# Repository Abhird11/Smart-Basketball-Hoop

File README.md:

This is our senior design project

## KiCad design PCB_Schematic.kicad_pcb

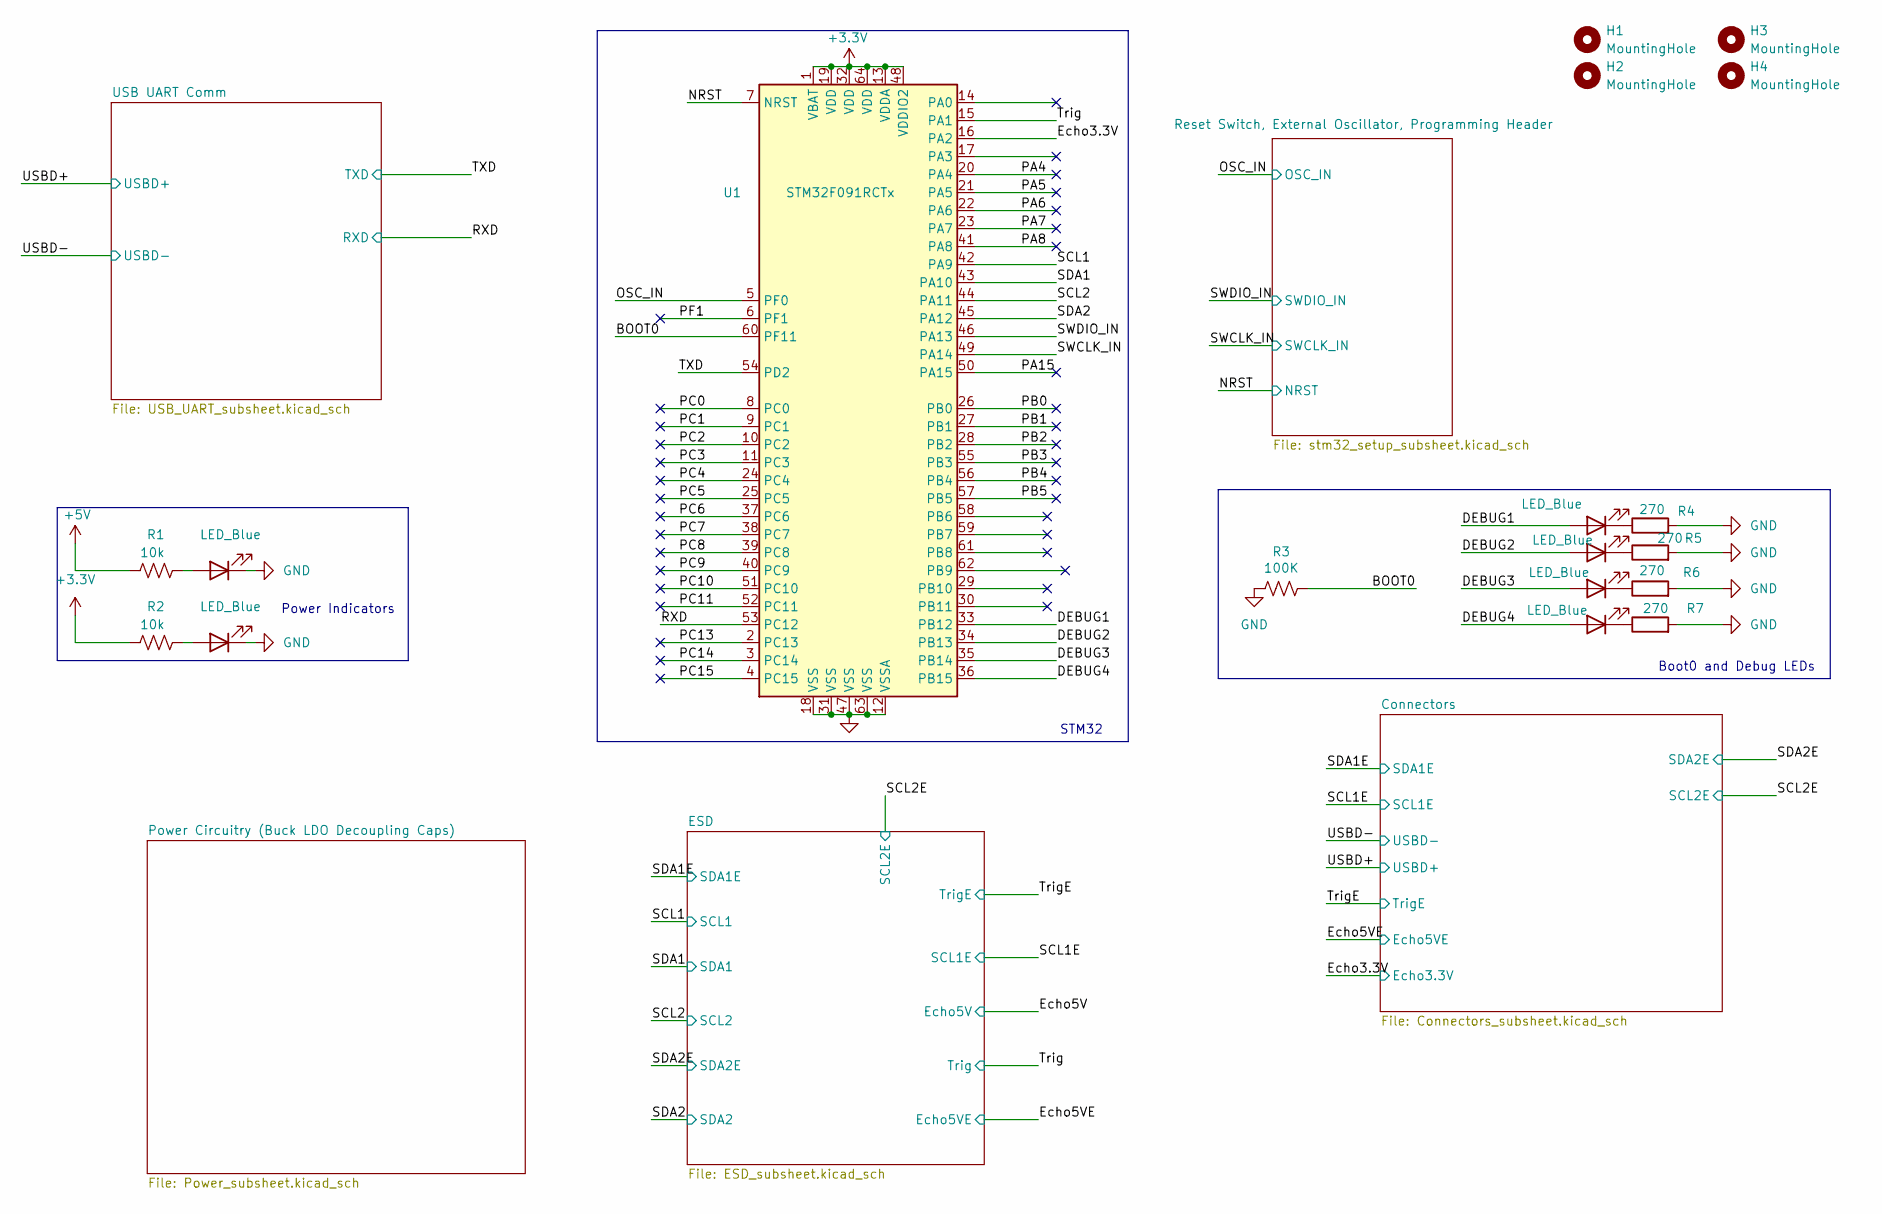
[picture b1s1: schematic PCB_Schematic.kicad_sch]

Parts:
D1, D2, D3, D4, D5, D6: LED_Blue; LED_0805_2012Metric_Pad1.15x1.40mm_HandSolder
H1, H2, H3, H4: MountingHole; MountingHole_2.2mm_M2
R1, R2: 10k; R_0805_2012Metric_Pad1.20x1.40mm_HandSolder
R3: 100K; R_0805_2012Metric_Pad1.20x1.40mm_HandSolder
R4, R5, R6, R7: 270; C_0805_2012Metric_Pad1.18x1.45mm_HandSolder
U1: STM32F091RCTx; LQFP-64_10x10mm_P0.5mm

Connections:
+3.3V: R2.2, U1.1 (VBAT), U1.13 (VDDA), U1.19 (VDD), U1.32 (VDD), U1.48 (VDDIO2), U1.64 (VDD); also elsewhere on the board
+5V: R1.2; also elsewhere on the board
/BOOT0: R3.1, U1.60 (PF11)
/DEBUG1: D3.2 (A), U1.33 (PB12)
/DEBUG2: D4.2 (A), U1.34 (PB13)
/DEBUG3: D5.2 (A), U1.35 (PB14)
/DEBUG4: D6.2 (A), U1.36 (PB15)
/Echo3.3V: U1.16 (PA2); also elsewhere on the board
/NRST: U1.7 (NRST); also elsewhere on the board
/OSC_IN: U1.5 (PF0); also elsewhere on the board
/PA4: U1.20 (PA4)
/PA5: U1.21 (PA5)
/PA6: U1.22 (PA6)
/PA7: U1.23 (PA7)
/PA8: U1.41 (PA8)
/PA15: U1.50 (PA15)
/PB0: U1.26 (PB0)
/PB1: U1.27 (PB1)
/PB2: U1.28 (PB2)
/PB3: U1.55 (PB3)
/PB4: U1.56 (PB4)
/PB5: U1.57 (PB5)
/PC0: U1.8 (PC0)
/PC1: U1.9 (PC1)
/PC2: U1.10 (PC2)
/PC3: U1.11 (PC3)
/PC4: U1.24 (PC4)
/PC5: U1.25 (PC5)
/PC6: U1.37 (PC6)
/PC7: U1.38 (PC7)
/PC8: U1.39 (PC8)
/PC9: U1.40 (PC9)
/PC10: U1.51 (PC10)
/PC11: U1.52 (PC11)
/PC13: U1.2 (PC13)
/PC14: U1.3 (PC14)
/PC15: U1.4 (PC15)
/PF1: U1.6 (PF1)
/RXD: U1.53 (PC12); also elsewhere on the board
/SCL1: U1.42 (PA9); also elsewhere on the board
/SCL2: U1.44 (PA11); also elsewhere on the board
/SDA1: U1.43 (PA10); also elsewhere on the board
/SDA2: U1.45 (PA12); also elsewhere on the board
/SWCLK_IN: U1.49 (PA14); also elsewhere on the board
/SWDIO_IN: U1.46 (PA13); also elsewhere on the board
/TXD: U1.54 (PD2); also elsewhere on the board
/Trig: U1.15 (PA1); also elsewhere on the board
GND: D1.1 (K), D2.1 (K), R3.2, R4.2, R5.2, R6.2, R7.2, U1.12 (VSSA), U1.18 (VSS), U1.31 (VSS), U1.47 (VSS), U1.63 (VSS); also elsewhere on the board
unnamed: D1.2 (A), R1.1
unnamed: D2.2 (A), R2.1
unnamed: D3.1 (K), R4.1
unnamed: D4.1 (K), R5.1
unnamed: D5.1 (K), R6.1
unnamed: D6.1 (K), R7.1

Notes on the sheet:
STM32
Boot0 and Debug LEDs
Power Indicators

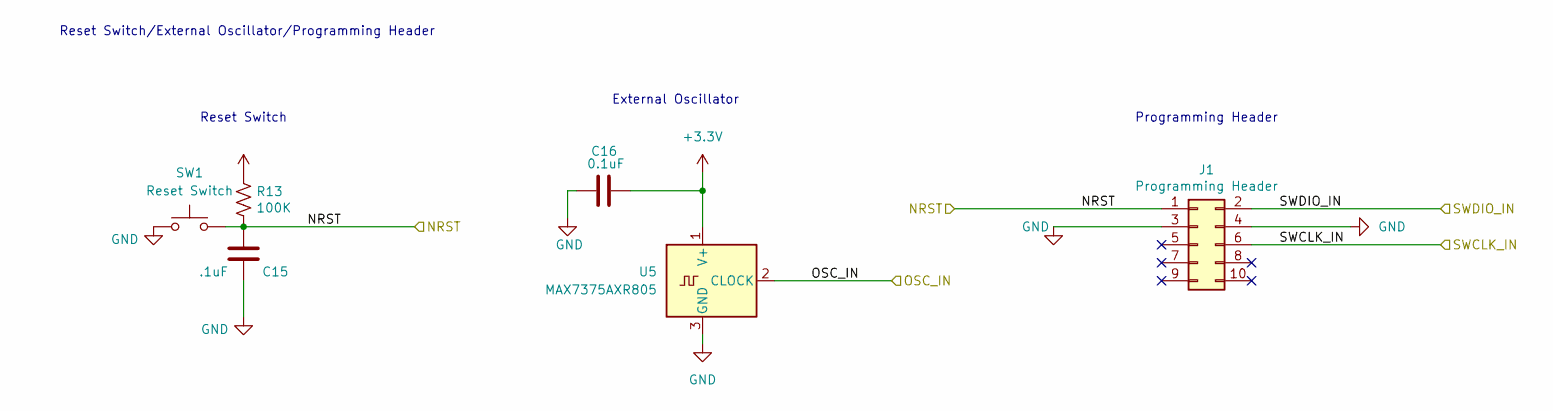
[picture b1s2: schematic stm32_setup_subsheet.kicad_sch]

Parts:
C15: .1uF; C_0805_2012Metric_Pad1.18x1.45mm_HandSolder
C16: 0.1uF; C_0805_2012Metric_Pad1.18x1.45mm_HandSolder
J1: Programming Header; IDC-Header_2x05_P2.54mm_Vertical
R13: 100K; R_0805_2012Metric_Pad1.20x1.40mm_HandSolder
SW1: Reset Switch; SW_TS04-66-55-BK-160-SMT
U5: MAX7375AXR805; SOT-323_SC-70_Handsoldering

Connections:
+3.3V: C16.2, R13.1, U5.1 (V+); also elsewhere on the board
/NRST: C15.1, J1.1, R13.2, SW1.2; also elsewhere on the board
/OSC_IN: U5.2 (CLOCK); also elsewhere on the board
/SWCLK_IN: J1.6; also elsewhere on the board
/SWDIO_IN: J1.2; also elsewhere on the board
GND: C15.2, C16.1, J1.3, J1.4, SW1.1, U5.3 (GND); also elsewhere on the board

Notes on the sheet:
Programming Header
Reset Switch/External Oscillator/Programming Header
Reset Switch
External Oscillator

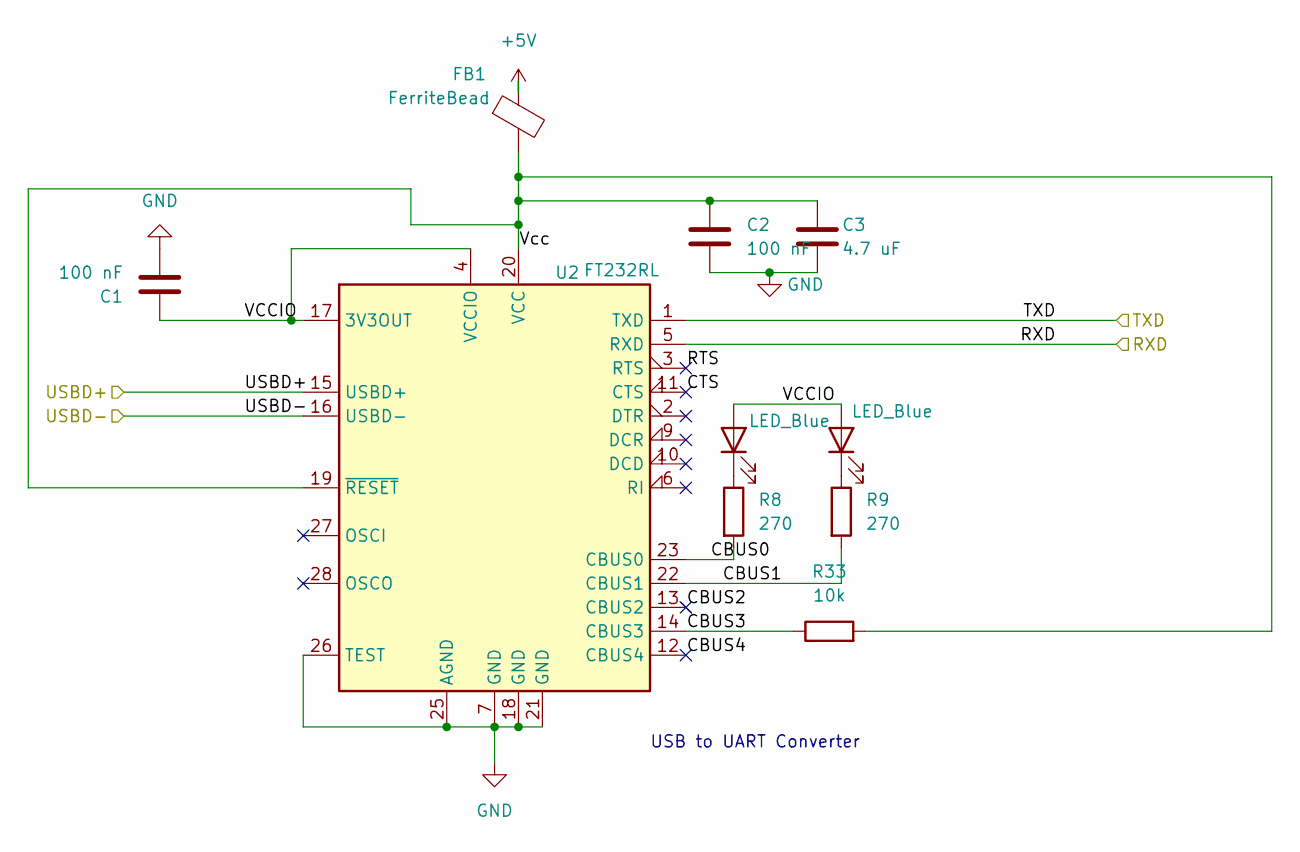
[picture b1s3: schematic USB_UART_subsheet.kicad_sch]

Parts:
C1, C2: 100 nF; C_0805_2012Metric_Pad1.18x1.45mm_HandSolder
C3: 4.7 uF; C_0805_2012Metric_Pad1.18x1.45mm_HandSolder
D7, D8: LED_Blue; LED_0805_2012Metric_Pad1.15x1.40mm_HandSolder
FB1: FerriteBead; FB
R8: 270; R_0805_2012Metric_Pad1.20x1.40mm_HandSolder
R9: 270; C_0805_2012Metric_Pad1.18x1.45mm_HandSolder
R33: 10k; R_0805_2012Metric_Pad1.20x1.40mm_HandSolder
U2: FT232RL; Project_FT232

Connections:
+5V: FB1.1; also elsewhere on the board
/RXD: U2.5 (RXD); also elsewhere on the board
/TXD: U2.1 (TXD); also elsewhere on the board
/USB UART Comm/CBUS0: R8.2, U2.23 (CBUS0)
/USB UART Comm/CBUS1: R9.2, U2.22 (CBUS1)
/USB UART Comm/CBUS2: U2.13 (CBUS2)
/USB UART Comm/CBUS3: R33.1, U2.14 (CBUS3)
/USB UART Comm/CBUS4: U2.12 (CBUS4)
/USB UART Comm/CTS: U2.11 (CTS)
/USB UART Comm/RTS: U2.3 (RTS)
/USB UART Comm/VCCIO: C1.1, D7.2 (A), D8.2 (A), U2.4 (VCCIO), U2.17 (3V3OUT)
/USB UART Comm/Vcc: C2.1, C3.1, FB1.2, R33.2, U2.19 (~RESET), U2.20 (VCC)
/USBD+: U2.15 (USBD+); also elsewhere on the board
/USBD-: U2.16 (USBD-); also elsewhere on the board
GND: C1.2, C2.2, C3.2, U2.7 (GND), U2.18 (GND), U2.21 (GND), U2.25 (AGND), U2.26 (TEST); also elsewhere on the board
unnamed: D7.1 (K), R8.1
unnamed: D8.1 (K), R9.1

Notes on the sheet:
USB to UART Converter

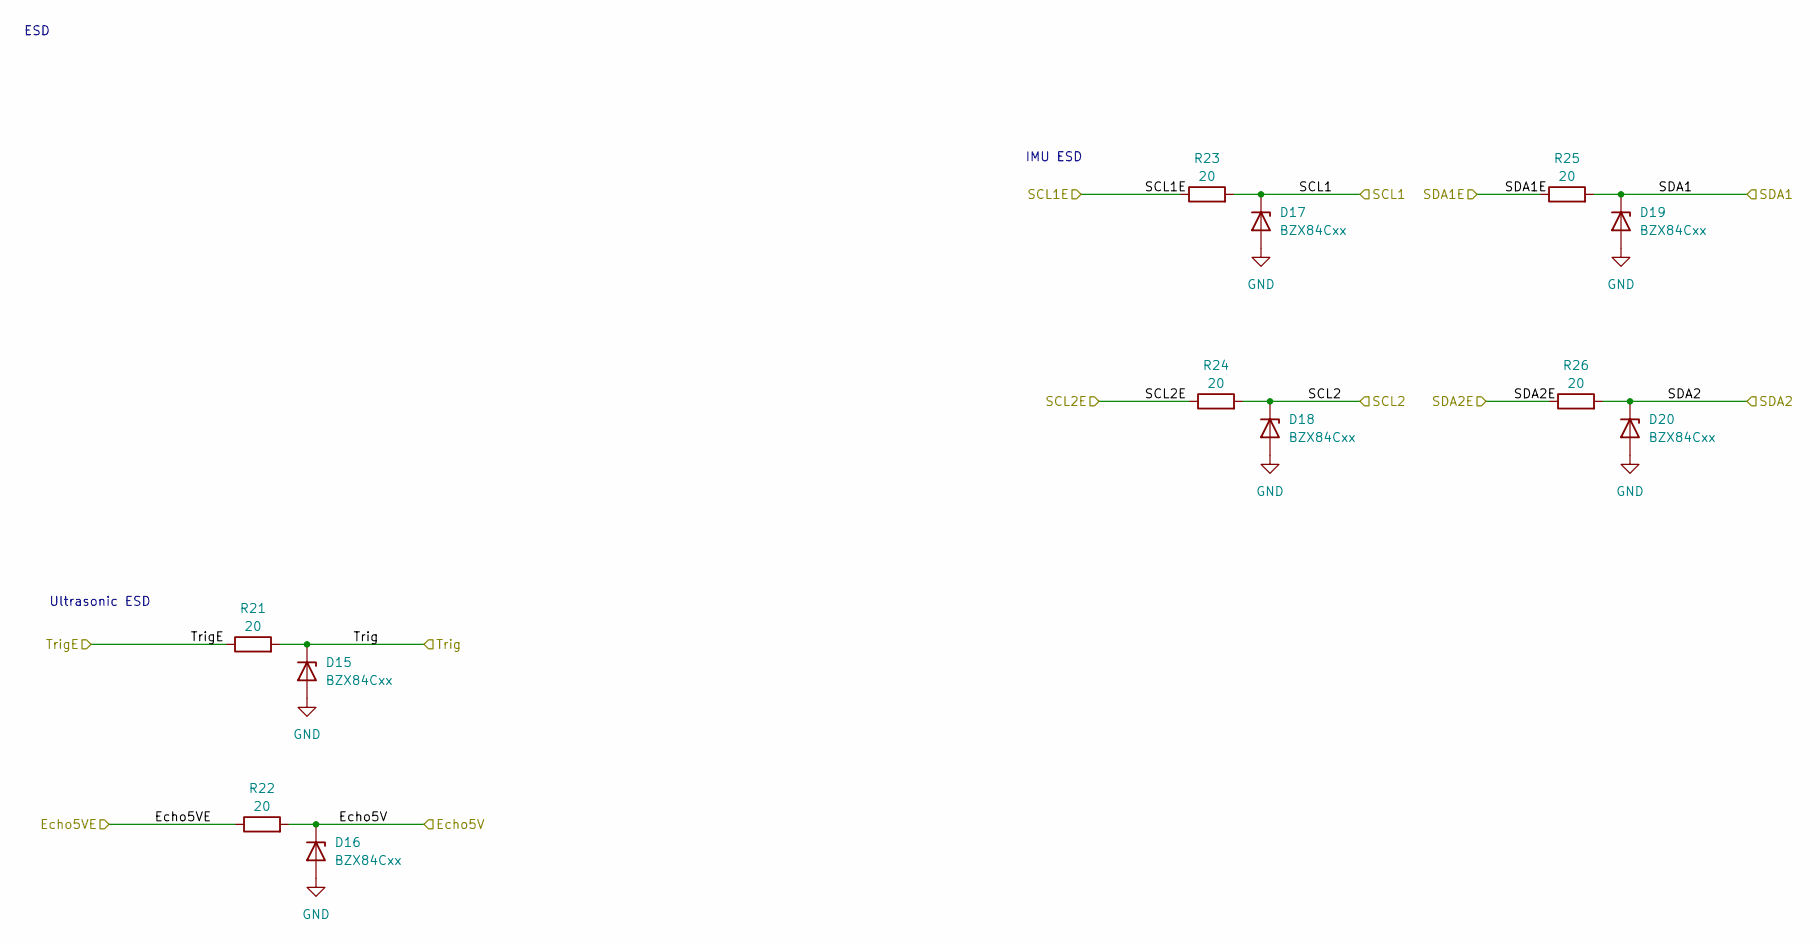
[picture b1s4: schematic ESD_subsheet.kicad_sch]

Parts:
D15, D16, D17, D18, D19, D20: BZX84Cxx; SOT-23
R21, R22, R23, R24, R25, R26: 20; R_0805_2012Metric_Pad1.20x1.40mm_HandSolder

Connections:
/Echo5V: D16.3 (K), R22.2
/Echo5VE: R22.1; also elsewhere on the board
/SCL1: D17.3 (K), R23.2; also elsewhere on the board
/SCL1E: R23.1; also elsewhere on the board
/SCL2: D18.3 (K), R24.2; also elsewhere on the board
/SCL2E: R24.1; also elsewhere on the board
/SDA1: D19.3 (K), R25.2; also elsewhere on the board
/SDA1E: R25.1; also elsewhere on the board
/SDA2: D20.3 (K), R26.2; also elsewhere on the board
/SDA2E: R26.1; also elsewhere on the board
/Trig: D15.3 (K), R21.2; also elsewhere on the board
/TrigE: R21.1; also elsewhere on the board
GND: D15.1 (A), D16.1 (A), D17.1 (A), D18.1 (A), D19.1 (A), D20.1 (A); also elsewhere on the board

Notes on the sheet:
IMU ESD
ESD
Ultrasonic ESD

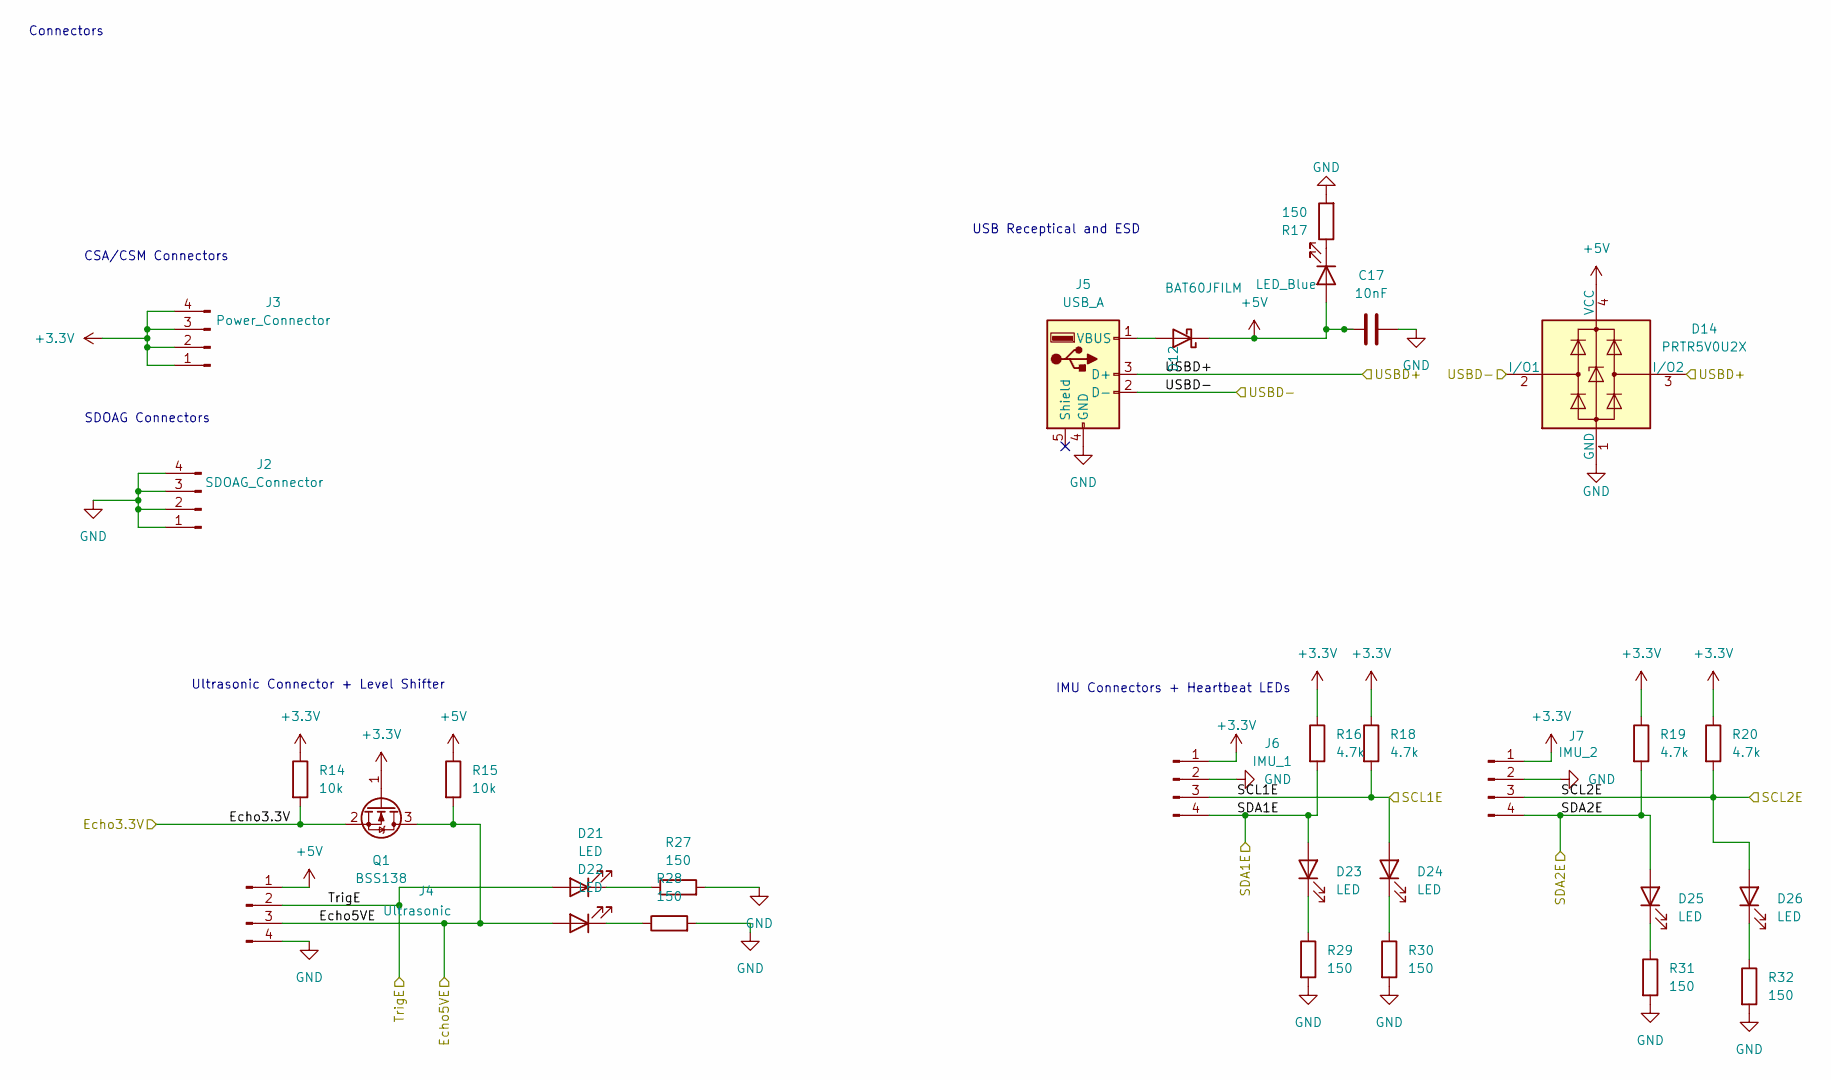
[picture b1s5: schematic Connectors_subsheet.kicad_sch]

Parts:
C17: 10nF; C_0805_2012Metric_Pad1.18x1.45mm_HandSolder
D12: BAT60JFILM; D_SOD-323_HandSoldering
D13: LED_Blue; LED_0805_2012Metric_Pad1.15x1.40mm_HandSolder
D14: PRTR5V0U2X; PRT
D21, D22, D23, D24, D25, D26: LED; LED_0805_2012Metric_Pad1.15x1.40mm_HandSolder
J2: SDOAG_Connector; CONN_B4B-XH-A_JSTProject
J3: Power_Connector; CONN_B4B-XH-A_JSTProject
J4: Ultrasonic; CONN_B4B-XH-A_JSTProject
J5: USB_A; USB_A_Receptacle_GCT_USB1046
J6: IMU_1; CONN_B4B-XH-A_JSTProject
J7: IMU_2; CONN_B4B-XH-A_JSTProject
Q1: BSS138; SOT-23-3
R14, R15: 10k; R_0805_2012Metric_Pad1.20x1.40mm_HandSolder
R16, R18, R19, R20: 4.7k; R_0805_2012Metric_Pad1.20x1.40mm_HandSolder
R17, R27, R28, R29, R30, R31, R32: 150; R_0805_2012Metric_Pad1.20x1.40mm_HandSolder

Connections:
+3.3V: J3.1, J3.2, J3.3, J3.4, J6.1, J7.1, Q1.1 (G), R14.1, R16.1, R18.1, R19.1, R20.1; also elsewhere on the board
+5V: C17.1, D12.1 (K), D13.2 (A), D14.4 (VCC), J4.1, R15.1; also elsewhere on the board
/Echo3.3V: Q1.2 (S), R14.2; also elsewhere on the board
/Echo5VE: D22.2 (A), J4.3, Q1.3 (D), R15.2; also elsewhere on the board
/SCL1E: D24.2 (A), J6.3, R18.2; also elsewhere on the board
/SCL2E: D26.2 (A), J7.3, R20.2; also elsewhere on the board
/SDA1E: D23.2 (A), J6.4, R16.2; also elsewhere on the board
/SDA2E: D25.2 (A), J7.4, R19.2; also elsewhere on the board
/TrigE: D21.2 (A), J4.2; also elsewhere on the board
/USBD+: D14.3 (I/O2), J5.3 (D+); also elsewhere on the board
/USBD-: D14.2 (I/O1), J5.2 (D-); also elsewhere on the board
GND: C17.2, D14.1 (GND), J2.1, J2.2, J2.3, J2.4, J4.4, J5.4 (GND), J6.2, J7.2, R17.2, R27.2, R28.2, R29.2, R30.2, R31.2, R32.2; also elsewhere on the board
unnamed: D12.2 (A), J5.1 (VBUS)
unnamed: D13.1 (K), R17.1
unnamed: D21.1 (K), R27.1
unnamed: D22.1 (K), R28.1
unnamed: D23.1 (K), R29.1
unnamed: D24.1 (K), R30.1
unnamed: D25.1 (K), R31.1
unnamed: D26.1 (K), R32.1

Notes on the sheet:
Ultrasonic Connector + Level Shifter
Connectors
SDOAG Connectors
USB Receptical and ESD
IMU Connectors + Heartbeat LEDs
CSA/CSM Connectors

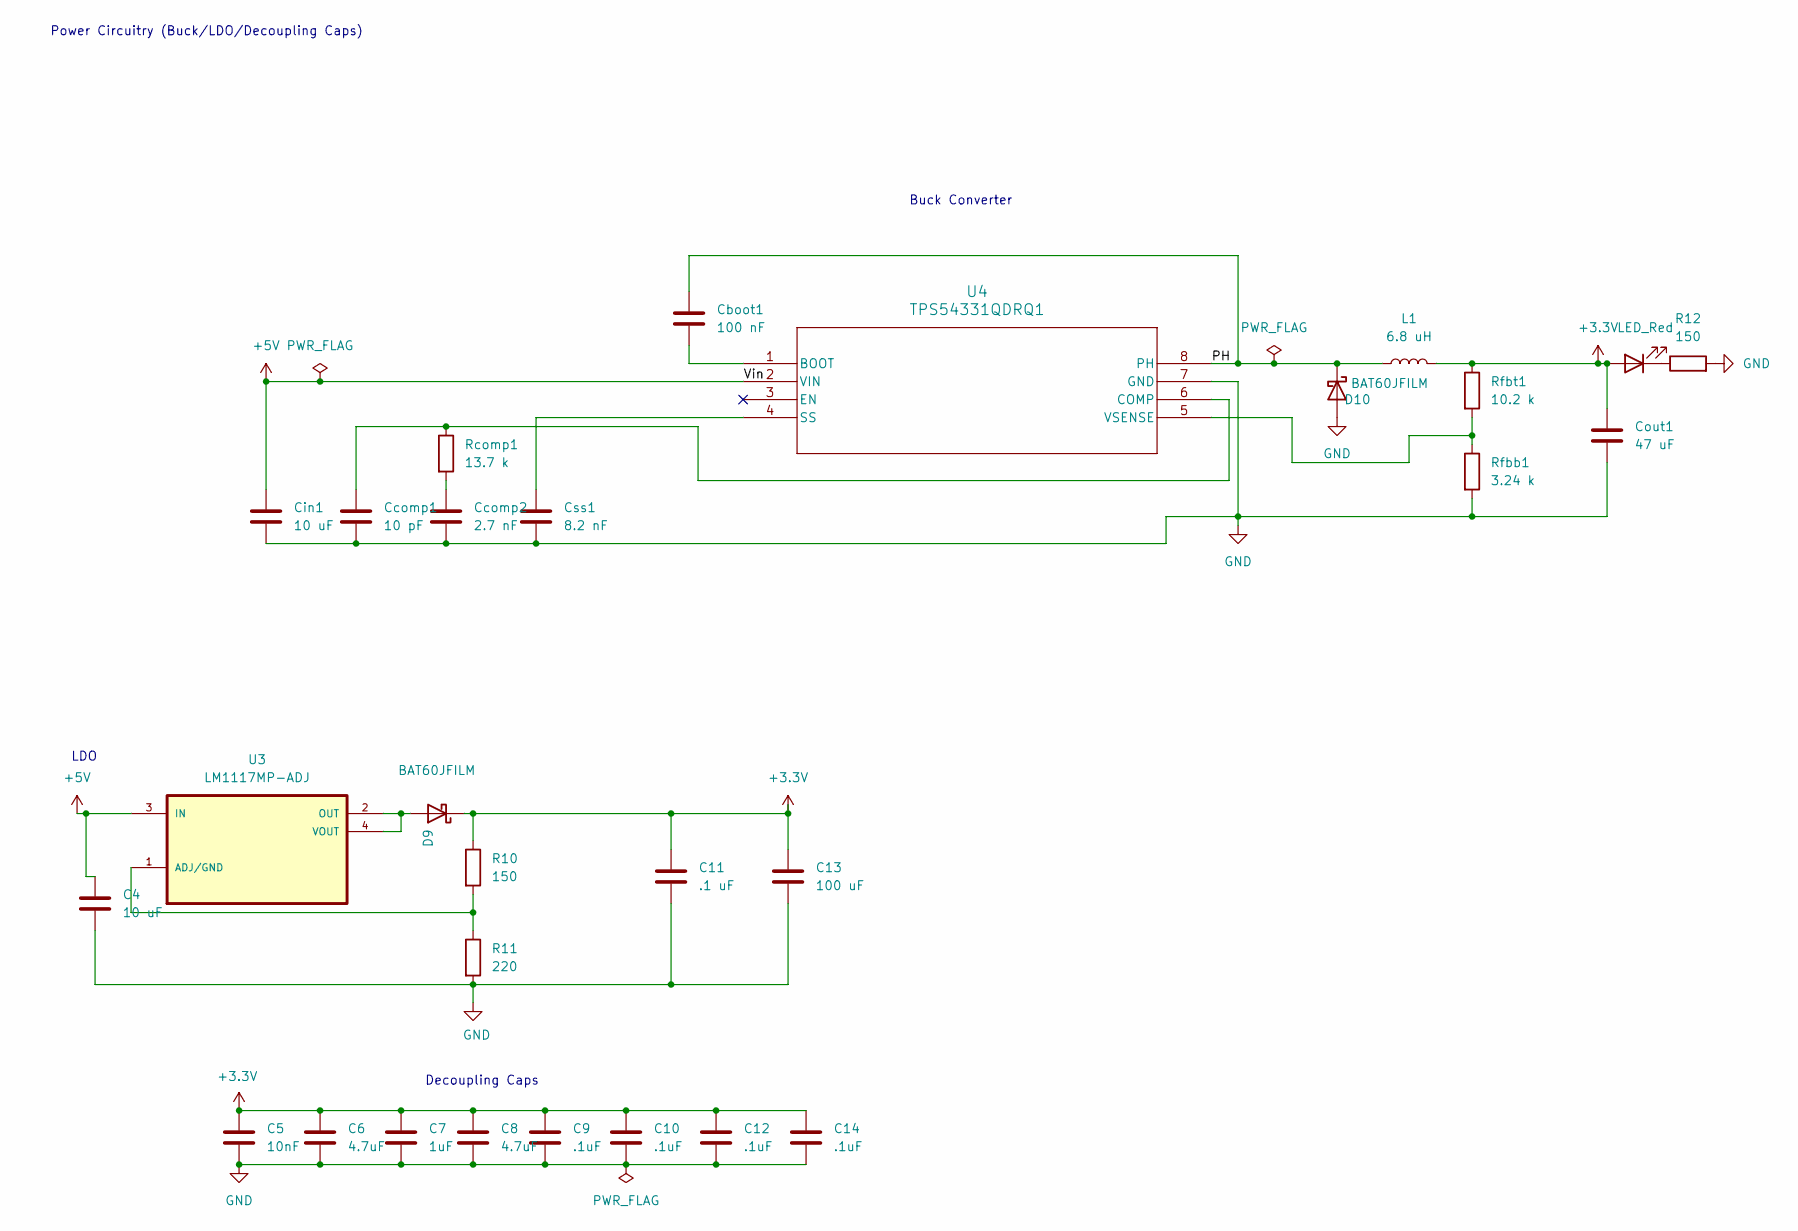
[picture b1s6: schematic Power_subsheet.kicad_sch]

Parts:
C4: 10 uF; C_0805_2012Metric_Pad1.18x1.45mm_HandSolder
C5: 10nF; C_0805_2012Metric_Pad1.18x1.45mm_HandSolder
C6, C8: 4.7uF; C_0805_2012Metric_Pad1.18x1.45mm_HandSolder
C7: 1uF; C_0805_2012Metric_Pad1.18x1.45mm_HandSolder
C9, C10, C12, C14: .1uF; C_0805_2012Metric_Pad1.18x1.45mm_HandSolder
C11: .1 uF; C_0805_2012Metric_Pad1.18x1.45mm_HandSolder
C13: 100 uF; C_0805_2012Metric_Pad1.18x1.45mm_HandSolder
Cboot1: 100 nF; R_0805_2012Metric_Pad1.20x1.40mm_HandSolder
Ccomp1: 10 pF; C_0805_2012Metric_Pad1.18x1.45mm_HandSolder
Ccomp2: 2.7 nF; C_0805_2012Metric_Pad1.18x1.45mm_HandSolder
Cin1: 10 uF; C_0805_2012Metric_Pad1.18x1.45mm_HandSolder
Cout1: 47 uF; C_0805_2012Metric_Pad1.18x1.45mm_HandSolder
Css1: 8.2 nF; C_0805_2012Metric_Pad1.18x1.45mm_HandSolder
D9: BAT60JFILM; D_SOD-323_HandSoldering
D10: BAT60JFILM; D_SOD-123
D11: LED_Red; LED_0805_2012Metric_Pad1.15x1.40mm_HandSolder
L1: 6.8 uH; inductor
R10, R12: 150; R_0805_2012Metric_Pad1.20x1.40mm_HandSolder
R11: 220; R_0805_2012Metric_Pad1.20x1.40mm_HandSolder
Rcomp1: 13.7 k; R_0805_2012Metric_Pad1.20x1.40mm_HandSolder
Rfbb1: 3.24 k; R_0805_2012Metric_Pad1.20x1.40mm_HandSolder
Rfbt1: 10.2 k; R_0805_2012Metric_Pad1.20x1.40mm_HandSolder
U3: LM1117MP-ADJ; REALWORKLDOFT
U4: TPS54331QDRQ1; Project_TPS

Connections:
+3.3V: C5.1, C6.1, C7.1, C8.1, C9.1, C10.1, C11.1, C12.1, C13.1, C14.1, Cout1.1, D9.1 (K), D11.2 (A), L1.2, R10.1, Rfbt1.1; also elsewhere on the board
+5V: C4.1, Cin1.1, U3.3 (IN), U4.2 (VIN); also elsewhere on the board
/Power Circuitry (Buck LDO Decoupling Caps)/PH: Cboot1.1, D10.1 (K), L1.1, U4.8 (PH)
GND: C4.2, C5.2, C6.2, C7.2, C8.2, C9.2, C10.2, C11.2, C12.2, C13.2, C14.2, Ccomp1.2, Ccomp2.2, Cin1.2, Cout1.2, Css1.2, D10.2 (A), R11.2, R12.2, Rfbb1.2, U4.7 (GND); also elsewhere on the board
unnamed: Ccomp2.1, Rcomp1.2
unnamed: D9.2 (A), U3.2 (OUT), U3.4 (VOUT)
unnamed: D11.1 (K), R12.1
unnamed: R10.2, R11.1, U3.1 (ADJ/GND)
unnamed: Cboot1.2, U4.1 (BOOT)
unnamed: Ccomp1.1, Rcomp1.1, U4.6 (COMP)
unnamed: Css1.1, U4.4 (SS)
unnamed: Rfbb1.1, Rfbt1.2, U4.5 (VSENSE)

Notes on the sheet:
Decoupling Caps
Buck Converter
Power Circuitry (Buck/LDO/Decoupling Caps)
LDO

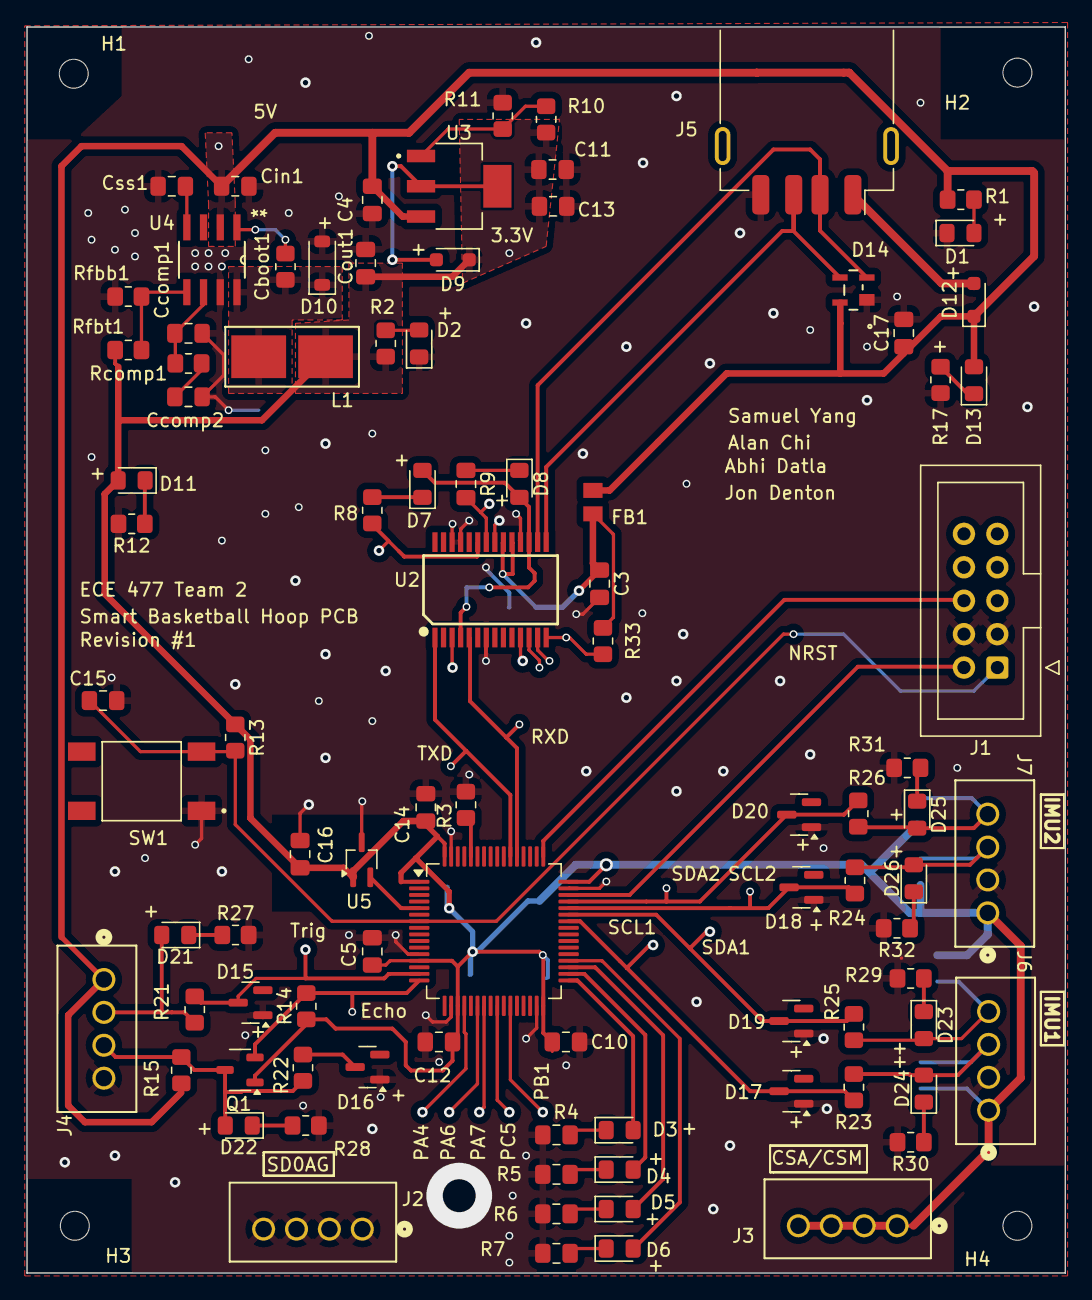
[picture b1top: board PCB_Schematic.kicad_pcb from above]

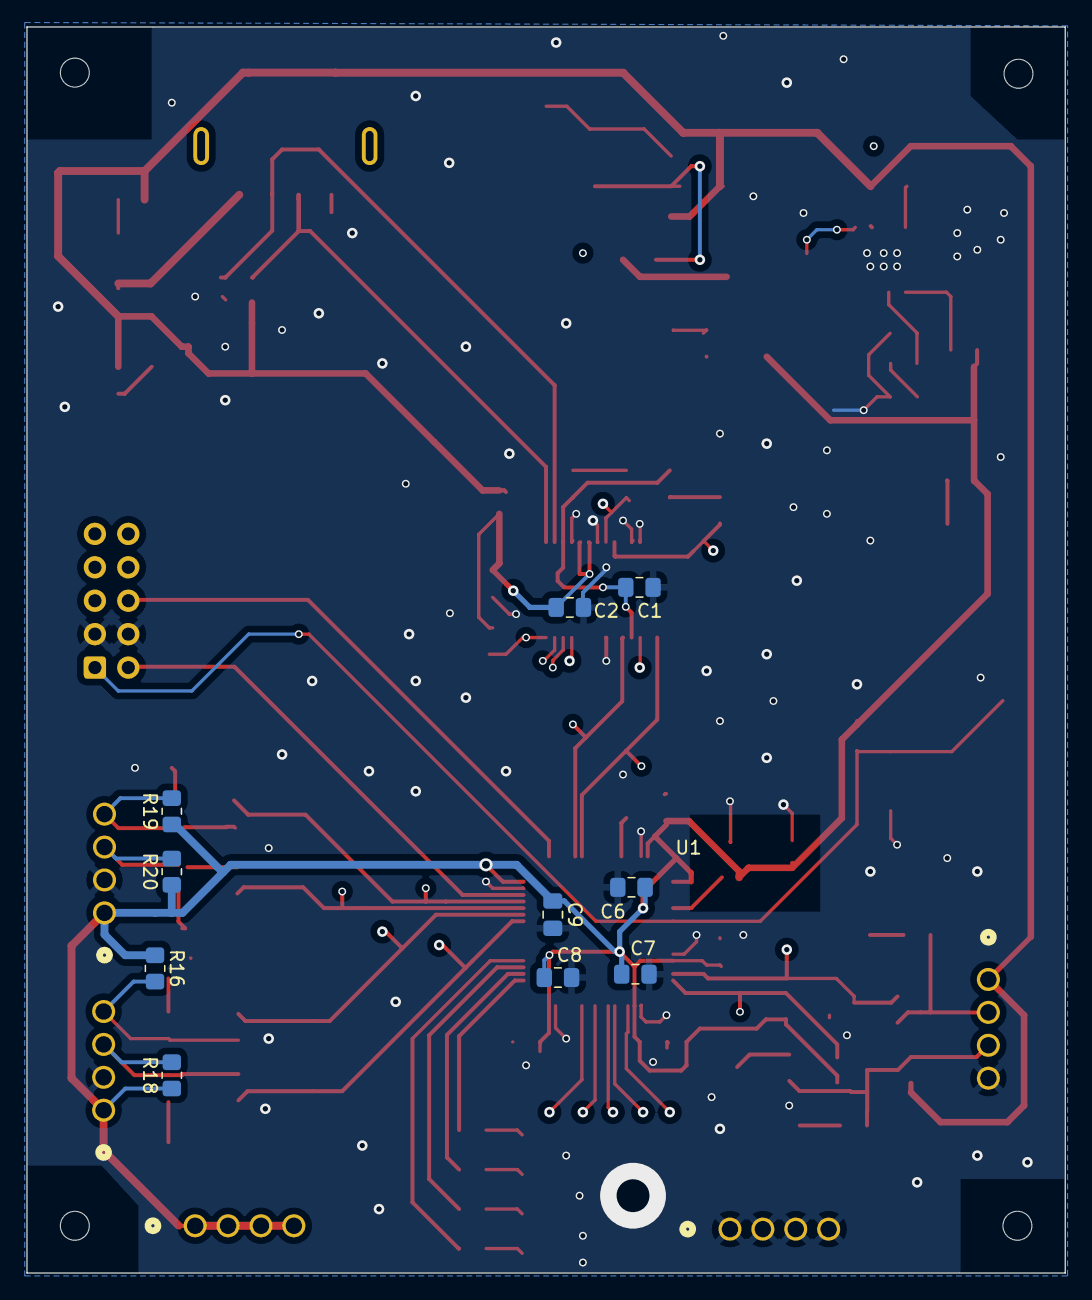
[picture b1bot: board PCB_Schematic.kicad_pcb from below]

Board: 2 copper layers, 78.9 x 94.7 mm, 105 parts (10 on the bottom side), 59 nets.
